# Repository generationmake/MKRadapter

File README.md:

# MKRadapter
combine Arduino MKR boards with Arduino Uno shields

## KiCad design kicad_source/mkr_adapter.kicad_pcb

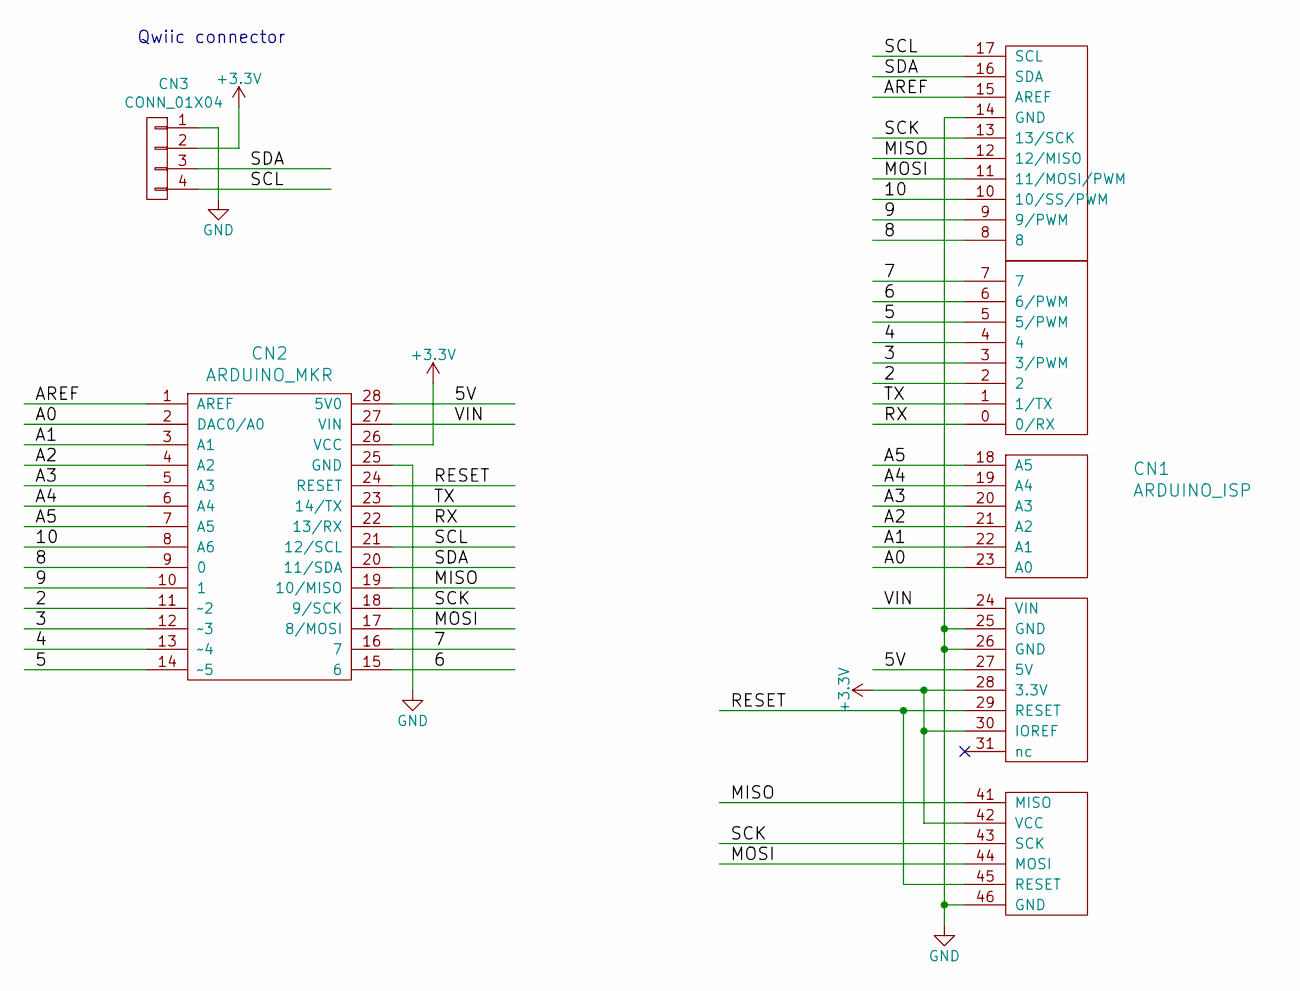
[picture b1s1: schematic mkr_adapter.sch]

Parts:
CN1: ARDUINO_ISP
CN2: ARDUINO_MKR
CN3: CONN_01X04; Connectors_JST_SM04B-SRSS-TB

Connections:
+3V3: CN1.28 (3.3V), CN1.30 (IOREF), CN1.42 (VCC), CN2.26 (VCC), CN3.2
/2: CN1.2, CN2.11 (~~2)
/3: CN1.3 (3/PWM), CN2.12 (~~3)
/4: CN1.4, CN2.13 (~~4)
/5: CN1.5 (5/PWM), CN2.14 (~~5)
/5V: CN1.27 (5V), CN2.28 (5V0)
/6: CN1.6 (6/PWM), CN2.15 (6)
/7: CN1.7, CN2.16 (7)
/8: CN1.8, CN2.9 (0)
/9: CN1.9 (9/PWM), CN2.10 (1)
/10: CN1.10 (10/SS/PWM), CN2.8 (A6)
/A0: CN1.23 (A0), CN2.2 (DAC0/A0)
/A1: CN1.22 (A1), CN2.3 (A1)
/A2: CN1.21 (A2), CN2.4 (A2)
/A3: CN1.20 (A3), CN2.5 (A3)
/A4: CN1.19 (A4), CN2.6 (A4)
/A5: CN1.18 (A5), CN2.7 (A5)
/AREF: CN1.15 (AREF), CN2.1 (AREF)
/MISO: CN1.12 (12/MISO), CN1.41 (MISO), CN2.19 (10/MISO)
/MOSI: CN1.11 (11/MOSI/PWM), CN1.44 (MOSI), CN2.17 (8/MOSI)
/RESET: CN1.29 (RESET), CN1.45 (RESET), CN2.24 (RESET)
/RX: CN1.0 (0/RX), CN2.22 (13/RX)
/SCK: CN1.13 (13/SCK), CN1.43 (SCK), CN2.18 (9/SCK)
/SCL: CN1.17 (SCL), CN2.21 (12/SCL), CN3.4
/SDA: CN1.16 (SDA), CN2.20 (11/SDA), CN3.3
/TX: CN1.1 (1/TX), CN2.23 (14/TX)
/VIN: CN1.24 (VIN), CN2.27 (VIN)
GND: CN1.14 (GND), CN1.25 (GND), CN1.26 (GND), CN1.46 (GND), CN2.25 (GND), CN3.1

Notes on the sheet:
Qwiic connector

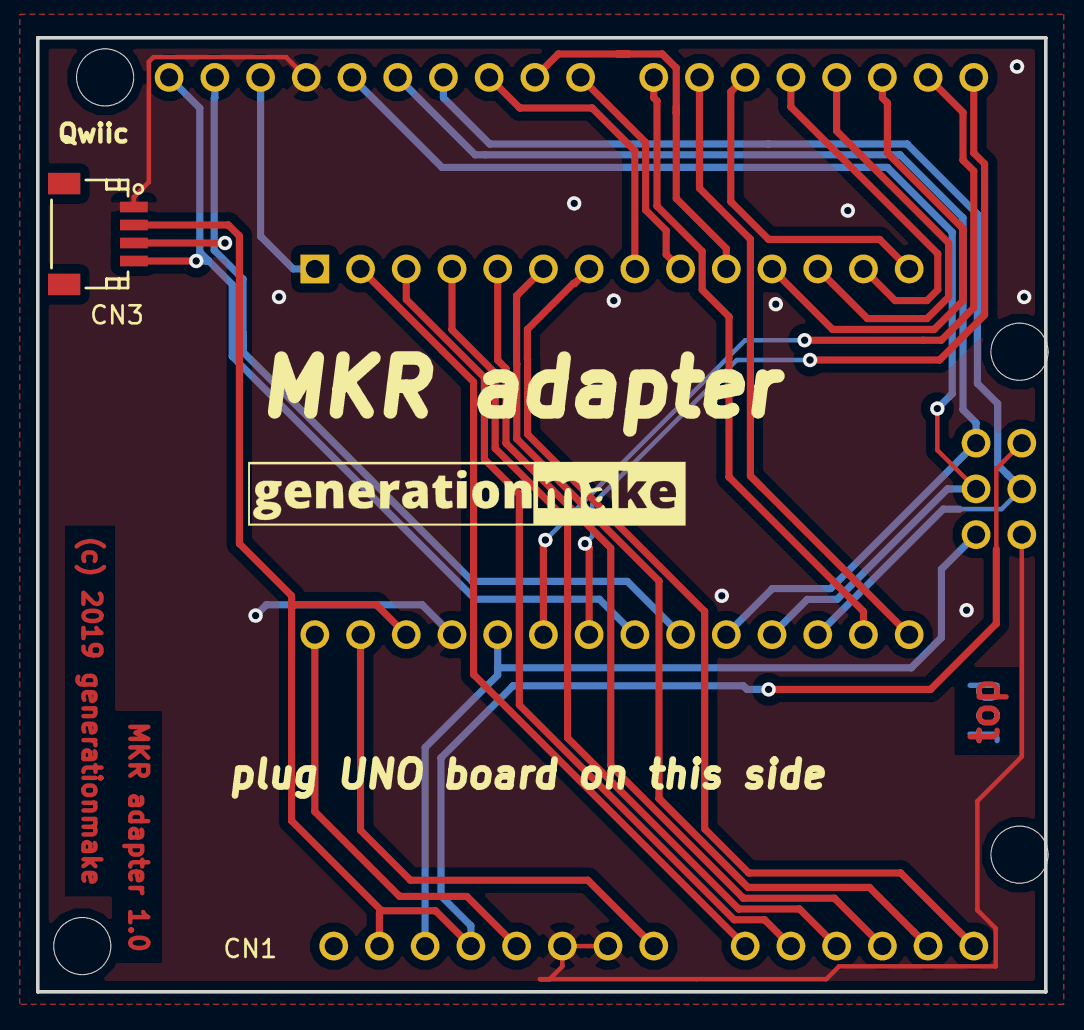
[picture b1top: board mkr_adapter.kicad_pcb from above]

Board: 2 copper layers, 56.0 x 53.0 mm, 3 parts (1 on the bottom side), 28 nets.

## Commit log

2020-01-14 added kicad project
2020-01-14 added images
2020-01-14 added pdf schematic

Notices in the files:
kicad_source/mkr_adapter.kicad_pcb:
(c) 2019 generationmake
